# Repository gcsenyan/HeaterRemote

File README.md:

# HeaterRemote
实在忍受不了每次洗澡时在卫生间脱了衣服才想起来忘记去开远在厨房的热水器这种情况了...于是做了个遥控器。
具体说明以后再写，如果现在就有人要借鉴，一定要注意，目前Arduino代码只有一个不安全的简单的版本，完全不加密也抵挡不了任何攻击。已经开始着手写采用AEAD加密认证的版本了。

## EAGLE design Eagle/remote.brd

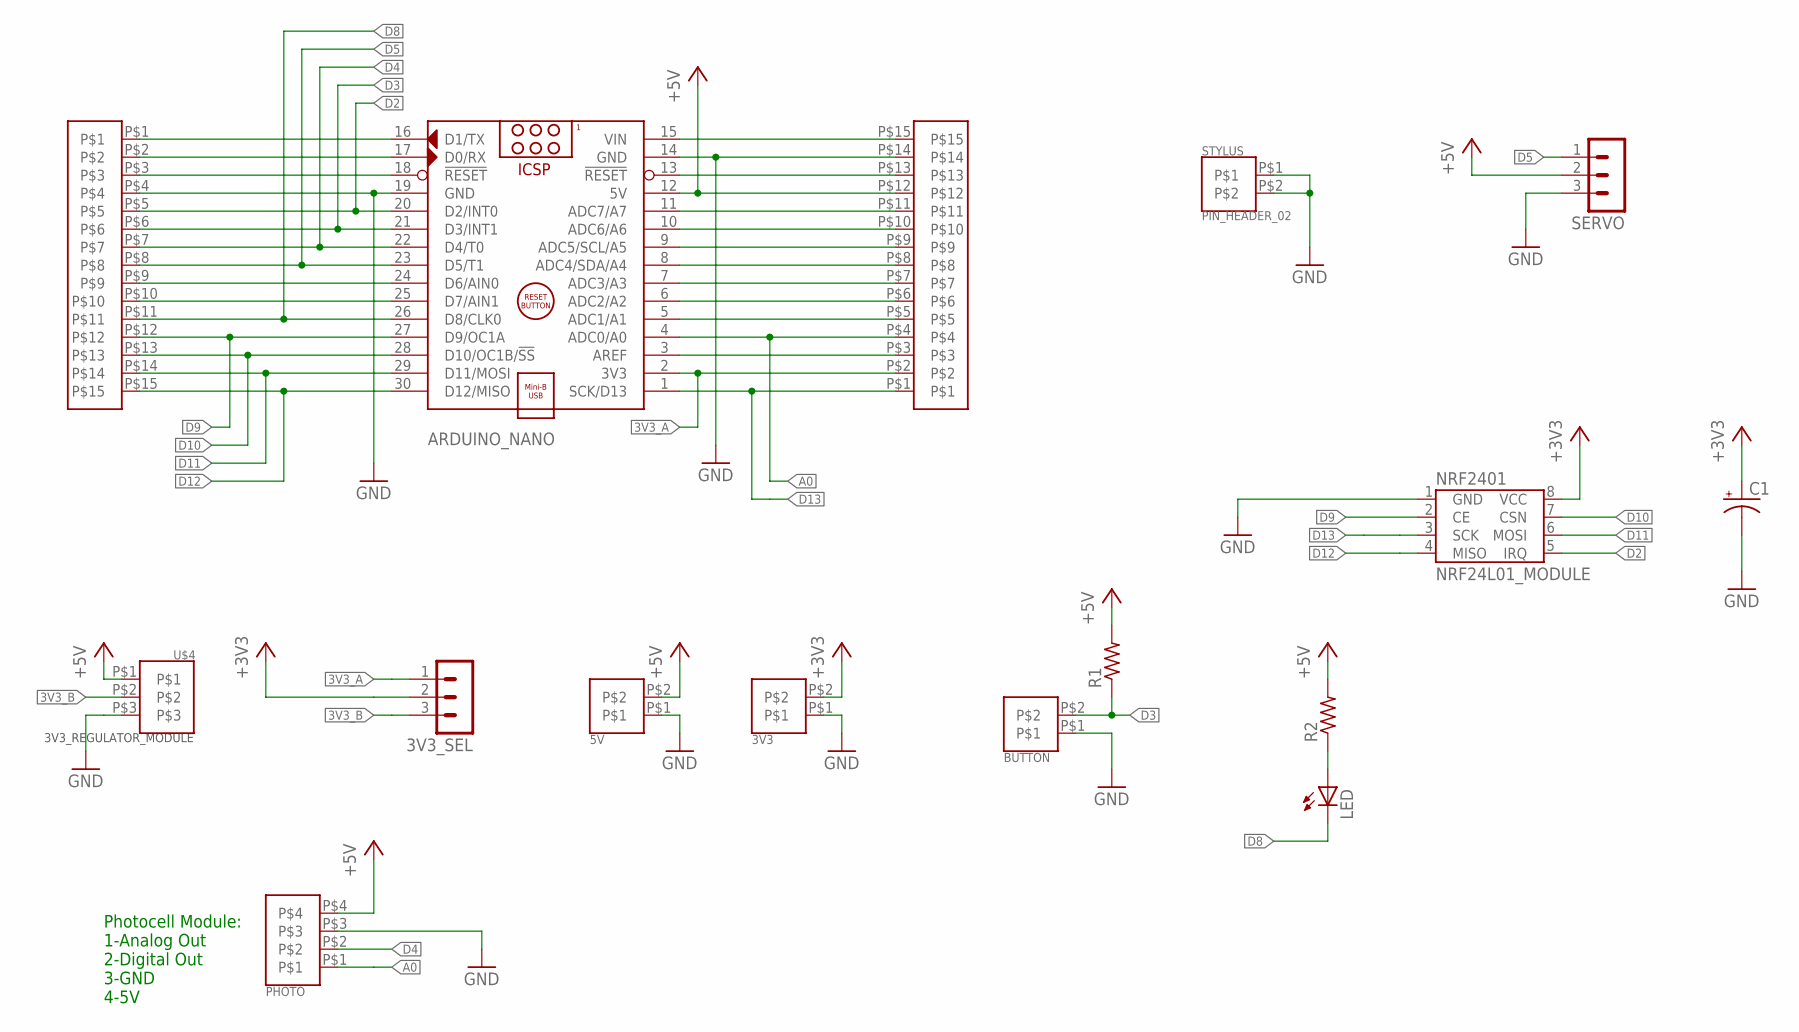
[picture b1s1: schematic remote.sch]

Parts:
3V3, 5V: PIN_HEADER_02
3V3_SEL: MA03-1
ARDUINO_NANO: ARDUINO_NANO_NO_HOLE; ARDUINO_NANO_B
BUTTON: PIN_HEADER_02
C1: CPOL-USE5-5; E5-5
LED: LED_HEADER; PIN_HEADER_02
NRF2401: NRF24L01_MODULE; NRF24_MODULE
PHOTO: PIN_HEADER_04
R1, R2: R-US_R0805; R0805
SERVO: MA03-1
STYLUS: PIN_HEADER_02
U$2, U$3: PIN_HEADER_15
U$4: 3V3_REGULATOR_MODULE

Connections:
3V3_A: 3V3_SEL.1, ARDUINO_NANO.2 (3V3), U$3.P$2
3V3_B: 3V3_SEL.3, U$4.P$2
+3V3: 3V3.P$2, 3V3_SEL.2, C1.+, NRF2401.8 (VCC)
+5V: 5V.P$2, ARDUINO_NANO.12 (5V), PHOTO.P$4, R1.2, R2.2, SERVO.2, U$3.P$12, U$4.P$1
A0: ARDUINO_NANO.4 (ADC0/A0), PHOTO.P$1, U$3.P$4
D2: ARDUINO_NANO.20 (D2/INT0), NRF2401.5 (IRQ), U$2.P$5
D3: ARDUINO_NANO.21 (D3/INT1), BUTTON.P$2, R1.1, U$2.P$6
D4: ARDUINO_NANO.22 (D4/T0), PHOTO.P$2, U$2.P$7
D5: ARDUINO_NANO.23 (D5/T1), SERVO.1, U$2.P$8
D8: ARDUINO_NANO.26 (D8/CLK0), LED.P$2 (C), U$2.P$11
D9: ARDUINO_NANO.27 (D9/OC1A), NRF2401.2 (CE), U$2.P$12
D10: ARDUINO_NANO.28 (D10/OC1B/!SS), NRF2401.7 (CSN), U$2.P$13
D11: ARDUINO_NANO.29 (D11/MOSI), NRF2401.6 (MOSI), U$2.P$14
D12: ARDUINO_NANO.30 (D12/MISO), NRF2401.4 (MISO), U$2.P$15
D13: ARDUINO_NANO.1 (SCK/D13), NRF2401.3 (SCK), U$3.P$1
GND: 3V3.P$1, 5V.P$1, ARDUINO_NANO.14 (GND), ARDUINO_NANO.19 (GND), BUTTON.P$1, C1.-, NRF2401.1 (GND), PHOTO.P$3, SERVO.3, STYLUS.P$1, STYLUS.P$2, U$2.P$4, U$3.P$14, U$4.P$3
unnamed: ARDUINO_NANO.16 (D1/TX), U$2.P$1
unnamed: ARDUINO_NANO.17 (D0/RX), U$2.P$2
unnamed: ARDUINO_NANO.18 (!RESET), U$2.P$3
unnamed: LED.P$1 (A), R2.1
unnamed: ARDUINO_NANO.24 (D6/AIN0), U$2.P$9
unnamed: ARDUINO_NANO.25 (D7/AIN1), U$2.P$10
unnamed: ARDUINO_NANO.3 (AREF), U$3.P$3
unnamed: ARDUINO_NANO.5 (ADC1/A1), U$3.P$5
unnamed: ARDUINO_NANO.6 (ADC2/A2), U$3.P$6
unnamed: ARDUINO_NANO.7 (ADC3/A3), U$3.P$7
unnamed: ARDUINO_NANO.8 (ADC4/SDA/A4), U$3.P$8
unnamed: ARDUINO_NANO.9 (ADC5/SCL/A5), U$3.P$9
unnamed: ARDUINO_NANO.10 (ADC6/A6), U$3.P$10
unnamed: ARDUINO_NANO.11 (ADC7/A7), U$3.P$11
unnamed: ARDUINO_NANO.13 (!RESET), U$3.P$13
unnamed: ARDUINO_NANO.15 (VIN), U$3.P$15

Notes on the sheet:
Photocell Module: 1-Analog Out 2-Digital Out 3-GND 4-5V

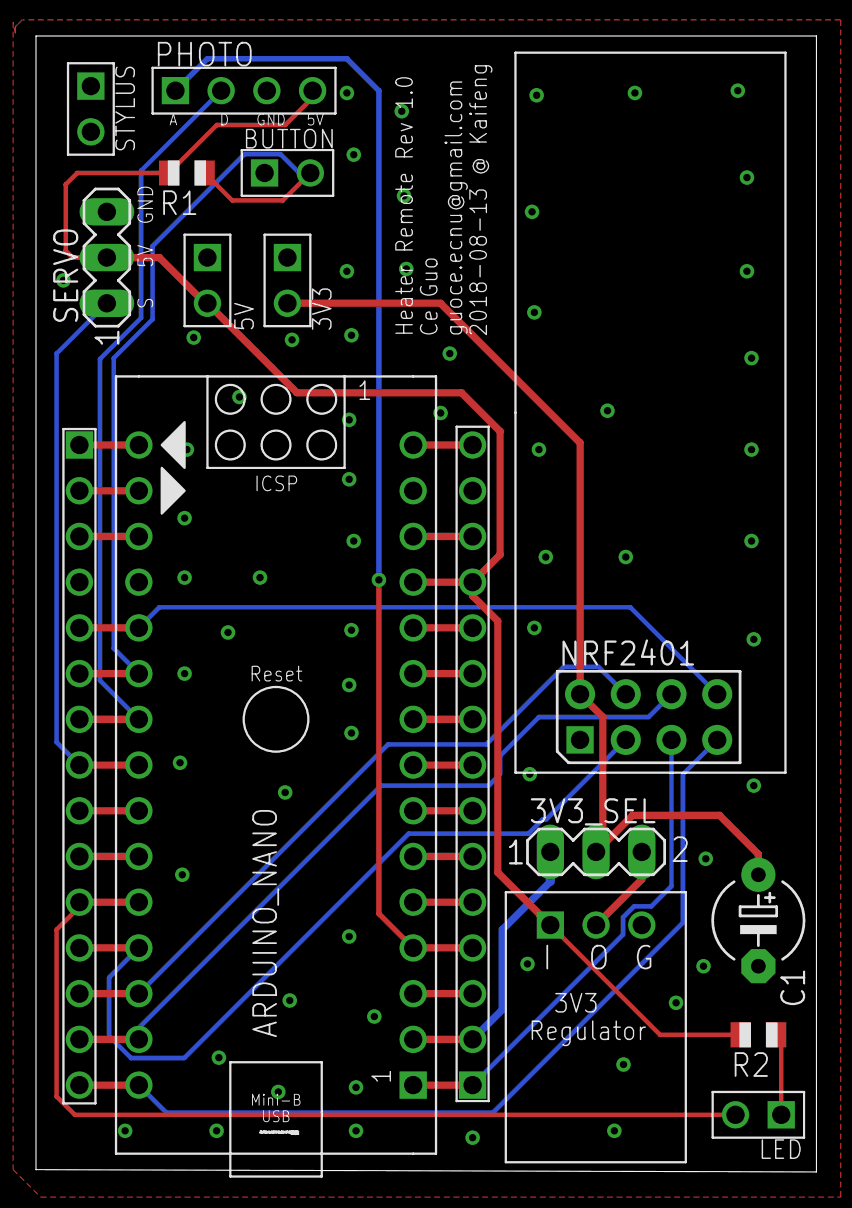
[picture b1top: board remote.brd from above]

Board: 2 copper layers, 43.4 x 63.1 mm, 16 parts (0 on the bottom side), 32 nets.

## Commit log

2018-08-22 Check point
2018-08-23 Runing out of time for secure approach. Let's do simple version first.
2018-08-23 Simple version finished
2018-08-23 Generated PCB image files
2018-08-24 Added botton control on the heater side for easier servo installation.
2018-08-24 Create LICENSE
